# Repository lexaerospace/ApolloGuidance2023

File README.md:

# ApolloGuidance2023
The Apollo Guidance System code and other information will be available here

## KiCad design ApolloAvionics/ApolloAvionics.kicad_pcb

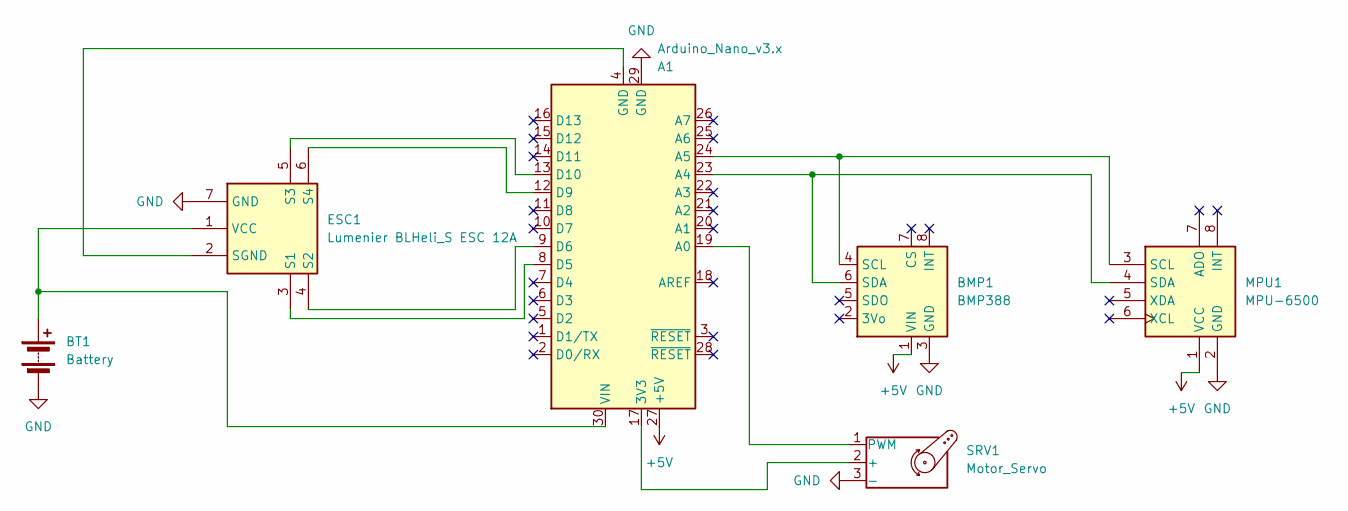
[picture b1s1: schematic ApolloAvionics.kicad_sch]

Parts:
A1: Arduino_Nano_v3.x; Arduino_Nano
BMP1: BMP388; PinSocket_1x08_P2.54mm_Vertical
BT1: Battery; PinSocket_1x02_P2.54mm_Vertical
ESC1: Lumenier BLHeli_S ESC 12A; PinSocket_1x07_P2.54mm_Vertical
MPU1: MPU-6500; PinSocket_1x08_P2.54mm_Vertical
SRV1: Motor_Servo; PinSocket_1x03_P2.54mm_Vertical

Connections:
+5V: A1.27 (+5V), BMP1.1 (VIN), MPU1.1 (VCC)
GND: A1.29 (GND), BMP1.3 (GND), BT1.2 (-), ESC1.7 (GND), MPU1.2 (GND), SRV1.3 (-)
unnamed: A1.17 (3V3), SRV1.2 (+)
unnamed: A1.19 (A0), SRV1.1 (PWM)
unnamed: A1.23 (A4), BMP1.6 (SDA), MPU1.4 (SDA)
unnamed: A1.24 (A5), BMP1.4 (SCL), MPU1.3 (SCL)
unnamed: A1.8 (D5), ESC1.3 (S1)
unnamed: A1.9 (D6), ESC1.4 (S2)
unnamed: A1.12 (D9), ESC1.6 (S4)
unnamed: A1.13 (D10), ESC1.5 (S3)
unnamed: A1.30 (VIN), BT1.1 (+), ESC1.1 (VCC)
unnamed: A1.4 (GND), ESC1.2 (SGND)

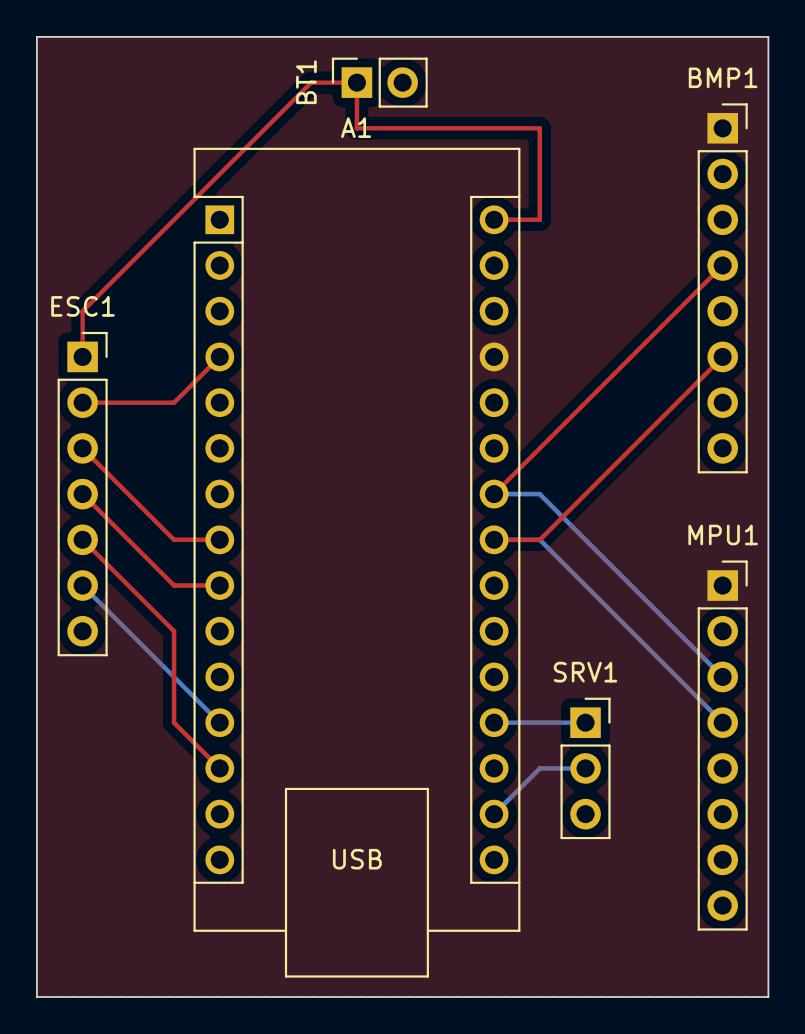
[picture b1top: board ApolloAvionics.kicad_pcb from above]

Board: 2 copper layers, 40.6 x 53.3 mm, 6 parts (0 on the bottom side), 12 nets.

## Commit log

2023-10-13 Base Betaflight Firmware
2023-11-04 Removed betaflight code
2024-02-05 Added sensor code
    Code for MPU and BMP Sensors (Orientation and Altitude Sensors)
2024-02-05 Fixed syntax
2024-02-07 Initial State Machine Code
2024-02-09 test
2024-02-09 PCB schematics
2024-02-09 Sensor schematics
2024-02-09 deleted hostname
2024-02-09 saved files
2024-02-14 Added Motor and Battery Schematics
2024-02-18 Added Mahoney Filter
2024-02-18 Changed state machine organization
2024-02-21 Added thrust equation
    Put thrust in stateMachine
2024-02-22 Removed comments
2024-02-23 Finalized PCB and setup velocity function
2024-02-23 fixed pcb
2024-02-26 Base MPU Sensor Test Code
    Added another folder for testing sensor accuracy
2024-02-27 Added Kalman Filter and BMP Readings
2024-02-28 Generated Gerber files
2024-02-28 Updated Gerber Files
2024-02-28 Created gerbers zip file
2024-03-04 Added MPU Velocity Calculations
2024-03-05 Finished velocity and sensor test code
2024-03-06 Added Motors class
2024-03-06 Added sensor test to main code
    Overall sensor readings are now much more accurate
2024-03-17 Added pulse width and motor run functions
2024-03-26 Added Guidance state code
